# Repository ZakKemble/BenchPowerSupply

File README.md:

Bench Power Supply
==================

A 7.5A adjustable output bench power supply designed to be used with a 19V laptop power supply.

https://blog.zakkemble.net/laptop-bench-power-supply/

---

Zak Kemble

contact@zakkemble.net

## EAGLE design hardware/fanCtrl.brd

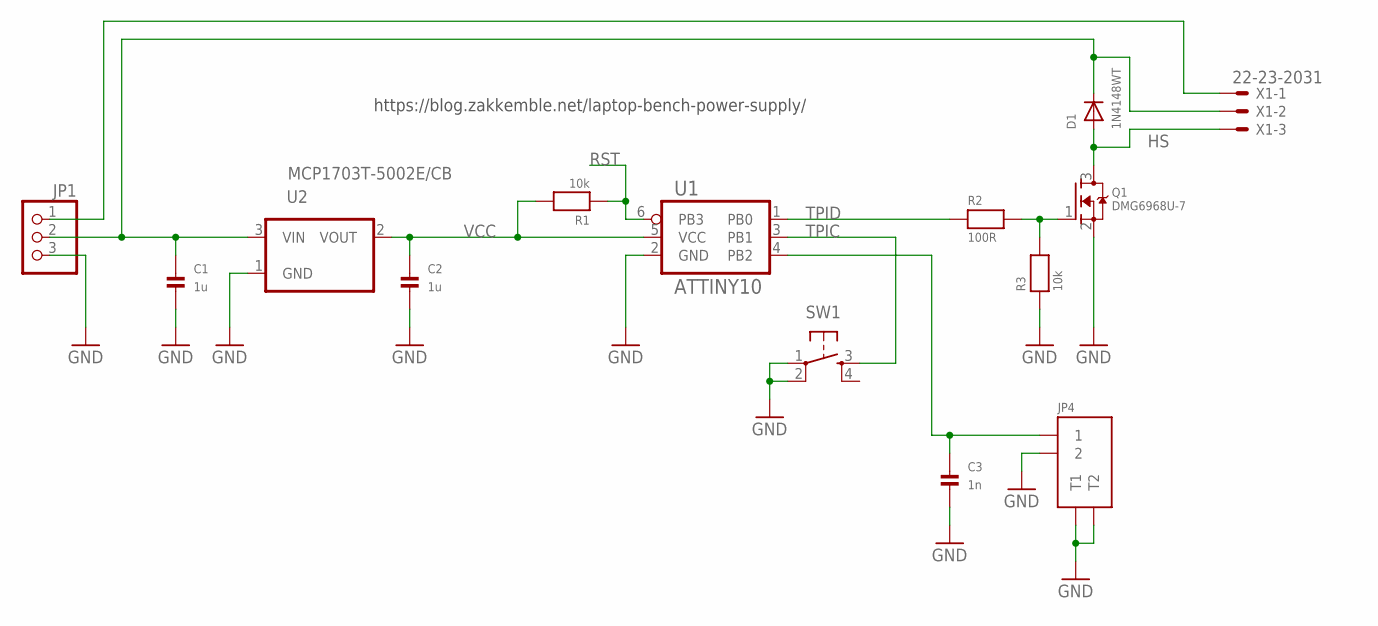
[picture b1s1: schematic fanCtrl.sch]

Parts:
C1, C2: 1u; _0603MP
C3: 1n; 0402_SMALL
D1: 1N4148WT; SOD-523
JP1: PINHD-1X3; 1X03
JP4: 2WAY
Q1: DMG6968U-7; SOT23-W
R1, R3: 10k; 0402_SMALL
R2: 100R; 0402_SMALL
SW1: SPST_TACTG75_3X4; TACT_SMD5
U1: ATTINY10; SOT23-6_SM_PAD
U2: MCP1703T-5002E/CB; SOT-23
X1: 22-23-2031

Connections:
GND: C1.2, C2.2, C3.2, JP1.3, JP4.P$2 (2), JP4.TAB$1 (T1), JP4.TAB$2 (T2), Q1.2 (S), R3.1, SW1.1, SW1.2 (P1), U1.2 (GND), U2.1 (GND)
HS: D1.A, Q1.3 (D), X1.3
unnamed: Q1.1 (G), R2.2, R3.2
unnamed: C3.1, JP4.P$1 (1), U1.4 (PB2)
unnamed: C1.1, D1.K (C), JP1.2, U2.3 (VIN), X1.2
unnamed: JP1.1, X1.1
RST: R1.1, U1.6 (PB3)
TPIC: SW1.3 (S), U1.3 (PB1)
TPID: R2.1, U1.1 (PB0)
VCC: C2.1, R1.2, U1.5 (VCC), U2.2 (VOUT)

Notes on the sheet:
https://blog.zakkemble.net/laptop-bench-power-supply/

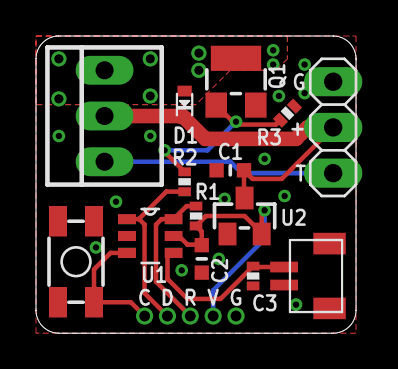
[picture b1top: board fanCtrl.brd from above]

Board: 2 copper layers, 17.8 x 16.5 mm, 14 parts (0 on the bottom side), 10 nets.

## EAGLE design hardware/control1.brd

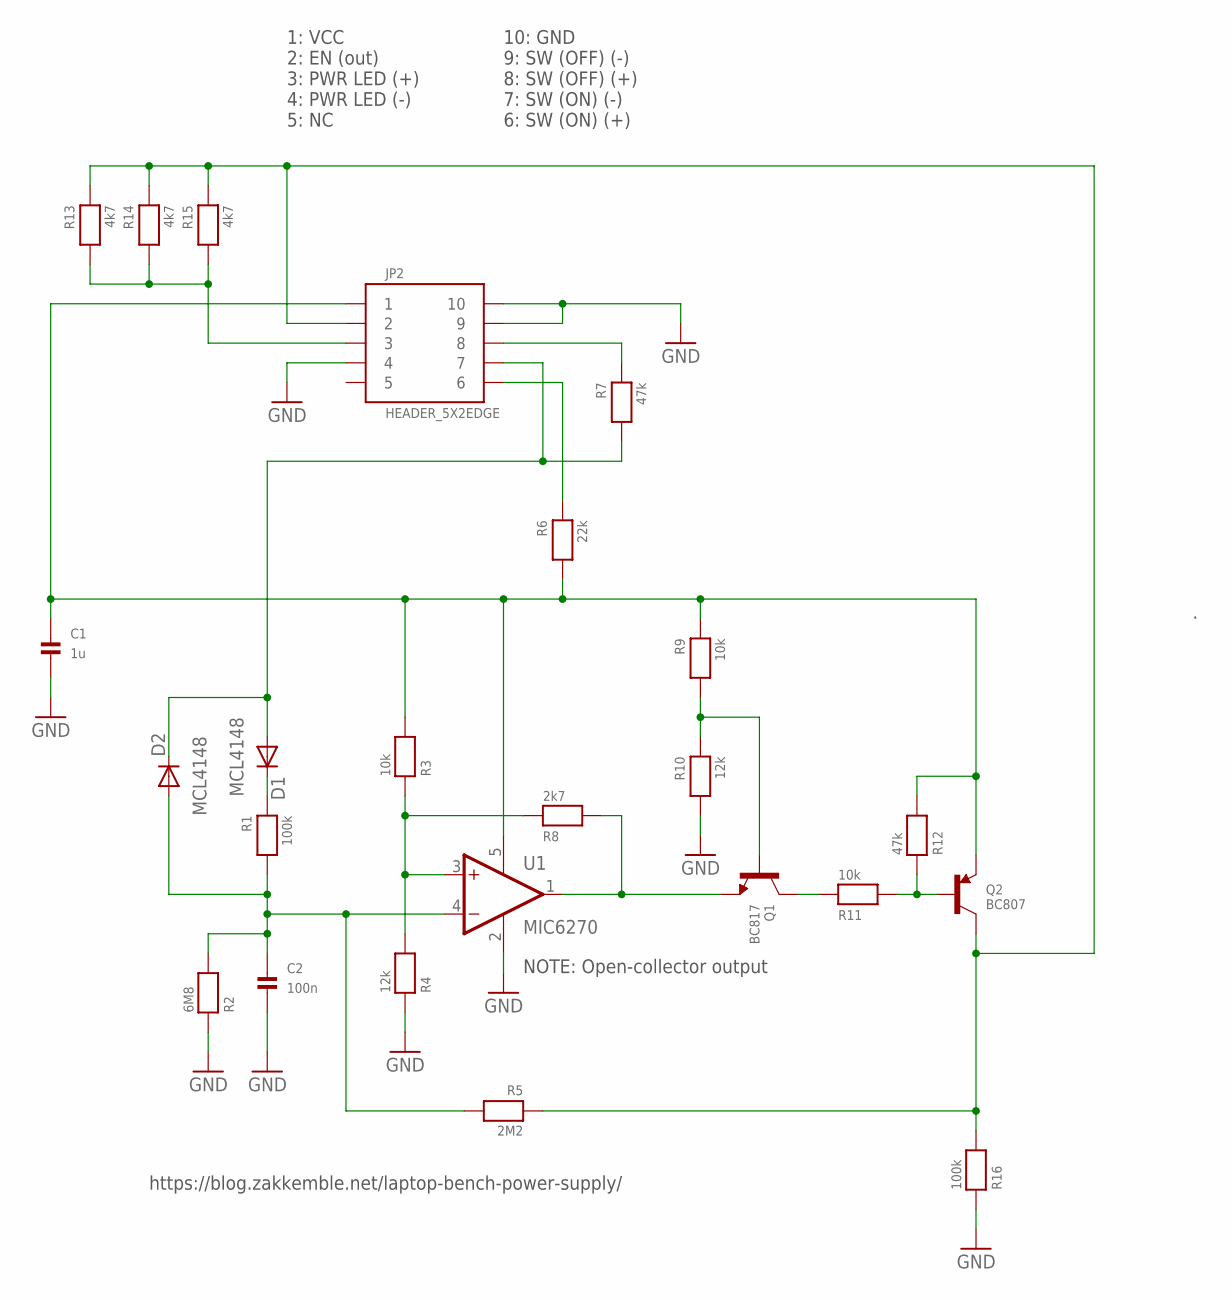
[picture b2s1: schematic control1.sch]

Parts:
C1: 1u; 0402
C2: 100n; _0603MP
D1, D2: MCL4148; MICROMELF-R
JP2: HEADER_5X2EDGE; HEADER_EDGE_5X2
Q1: BC817; SOT23-WIDE
Q2: BC807; SOT23-WIDE
R1, R16: 100k; 0402
R2: 6M8; 0402
R3, R9, R11: 10k; 0402
R4, R10: 12k; 0402
R5: 2M2; 0402
R6: 22k; 0402
R7, R12: 47k; 0402
R8: 2k7; 0402
R13, R14, R15: 4k7; 0402
U1: MIC6270; SOT95P275X110-5N

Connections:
GND: C1.2, C2.2, JP2.4, JP2.9, JP2.10, R2.1, R4.1, R10.2, R16.1, U1.2 (GND)
unnamed: C1.1, JP2.1, Q2.2 (E), R3.2, R6.2, R9.1, R12.2, U1.5 (V+)
unnamed: JP2.8, R7.1
unnamed: JP2.3, R13.2, R14.2, R15.2
unnamed: R3.1, R4.2, R8.1, U1.3 (+IN)
unnamed: C2.1, D2.A, R1.2, R2.2, R5.2, U1.4 (-IN)
unnamed: JP2.6, R6.1
unnamed: JP2.2, Q2.3 (C), R5.1, R13.1, R14.1, R15.1, R16.2
unnamed: Q1.3 (C), R11.1
unnamed: Q2.1 (B), R11.2, R12.1
unnamed: Q1.2 (E), R8.2, U1.1 (OUT)
unnamed: Q1.1 (B), R9.2, R10.1
unnamed: D1.A, D2.C, JP2.7, R7.2
unnamed: D1.C, R1.1

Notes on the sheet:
NOTE: Open-collector output
1: VCC 2: EN (out) 3: PWR LED (+) 4: PWR LED (-) 5: NC
10: GND 9: SW (OFF) (-) 8: SW (OFF) (+) 7: SW (ON) (-) 6: SW (ON) (+)
https://blog.zakkemble.net/laptop-bench-power-supply/

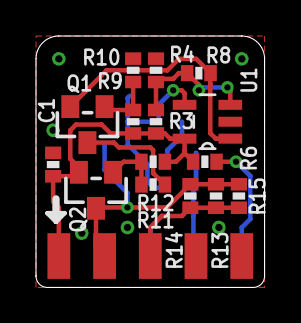
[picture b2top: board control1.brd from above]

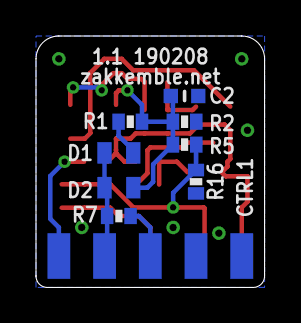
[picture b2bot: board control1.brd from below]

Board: 2 copper layers, 12.7 x 14.0 mm, 24 parts (8 on the bottom side), 14 nets.

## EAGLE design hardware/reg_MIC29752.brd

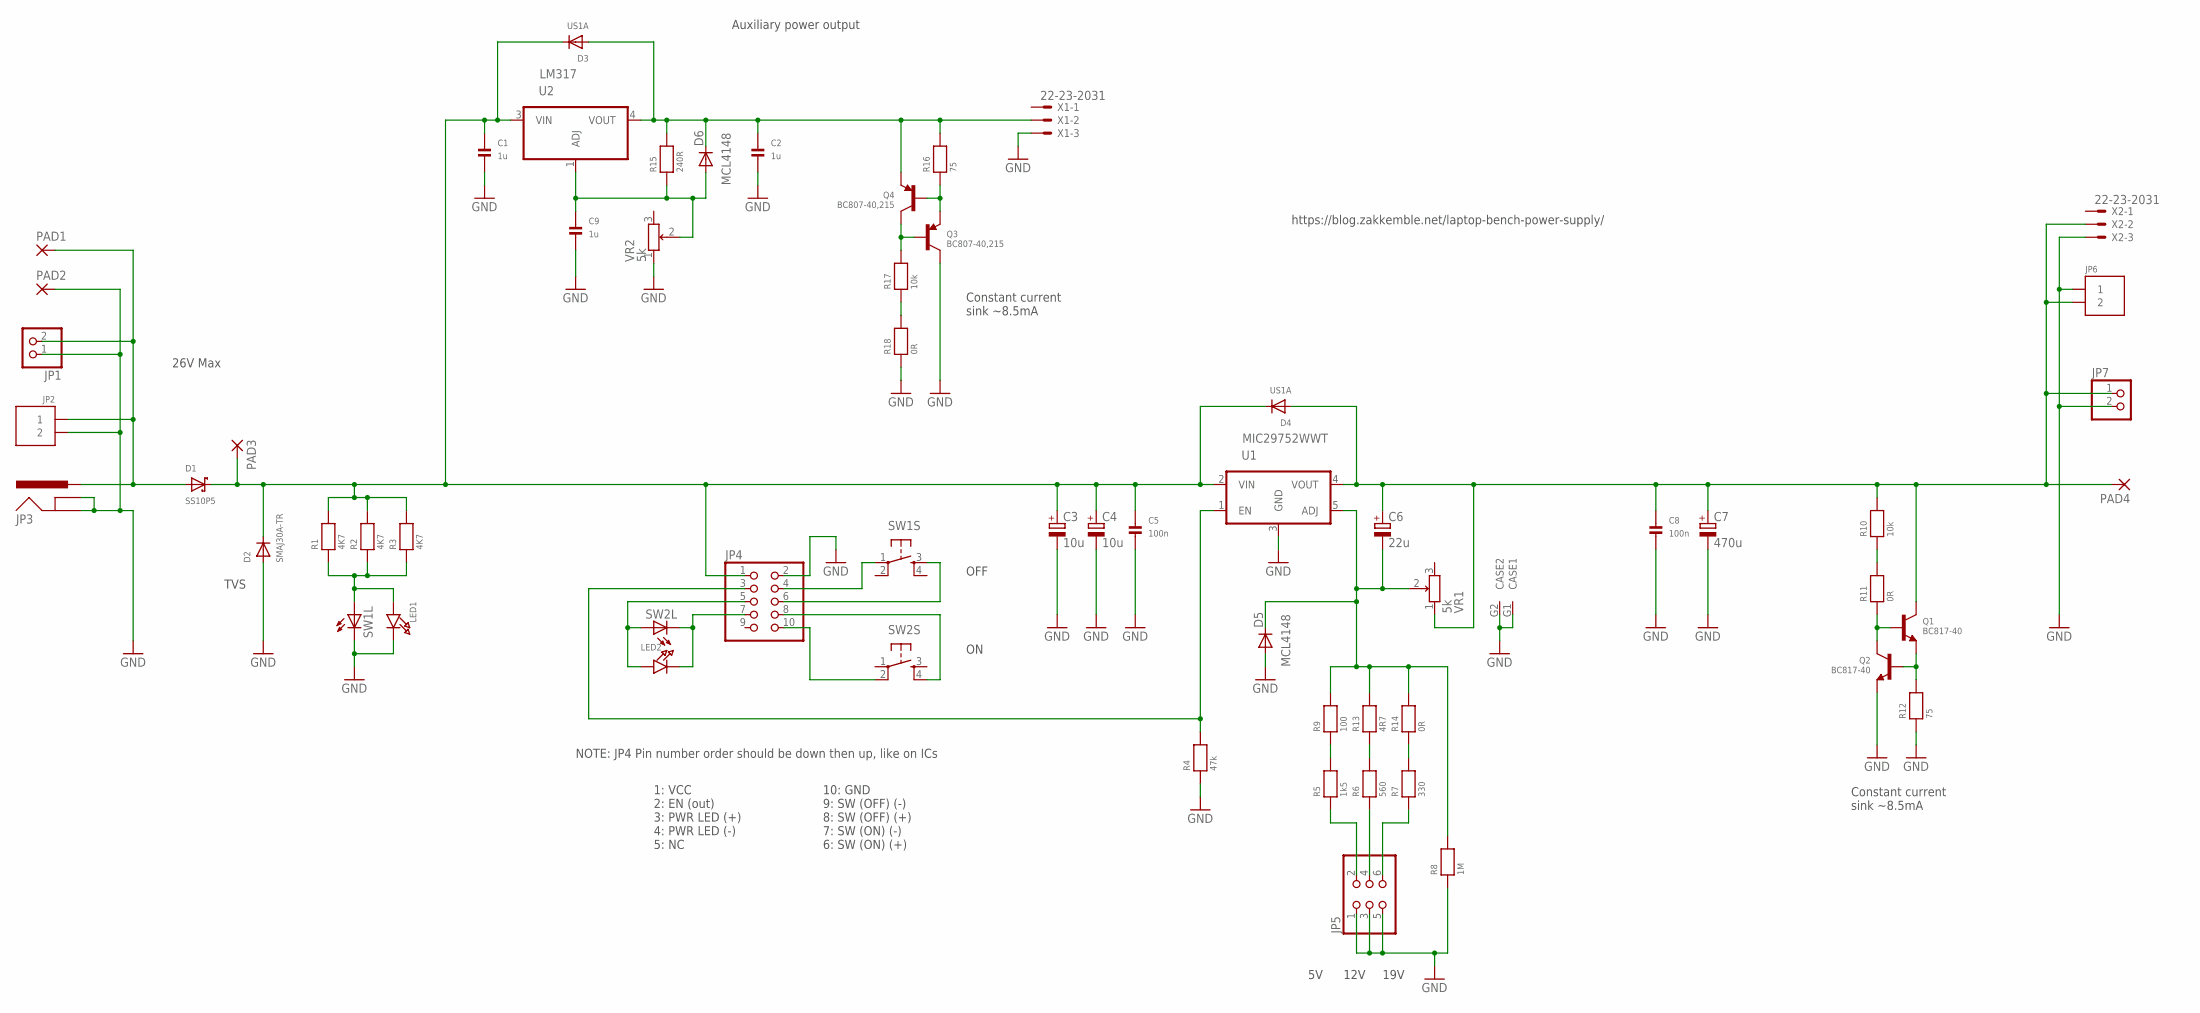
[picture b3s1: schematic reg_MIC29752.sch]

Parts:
C1, C2, C9: 1u; 0805_NO_OUTLINE
C3, C4: 10u; E2-5
C5, C8: 100n; _0603MP
C6: 22u; E2-4
C7: 470u; E5-10,5
D1: SS10P5; TO-277A
D2: SMAJ30A-TR; SMADIODE
D3, D4: US1A; SMADIODE
D5, D6: MCL4148; MICROMELF-R
JP1, JP7: PINHD-1X2; 1X02
JP2, JP6: TERM_BLOCK_2WAY; TERM_2WAY
JP3: POWER_JACKPTH_HIGHCURRENT; POWER_JACK_PTH_HIGHCURRENT
JP4: PINHD-2X5; 2X05
JP5: PINHD-2X3; 2X03
LED1, LED2: LED0603_NOOUTLINE; CHIPLED_0603_NOOUTLINE
PAD1, PAD2, PAD3, PAD4: WIREPAD-3.81,2SCREW-3MM; SCREWPAD-3MM
Q1: BC817-40; SOT23-W
Q2: BC817-40; SOT23-WIDE
Q3: BC807-40,215; SOT23-W
Q4: BC807-40,215; SOT23-WIDE
R1, R2, R3: 4K7; 0402
R4: 47k; 0402
R5: 1k5; 0402
R6: 560; 0402
R7: 330; 0402
R8: 1M; 0402
R9: 100; 0402
R10, R17: 10k; 0402
R11, R14, R18: 0R; 0402
R12, R16: 75; 0402
R13: 4R7; 0402
R15: 240R; 0402
SW1, SW2: SPST_TACT_LED12MM_TH; TACT_TH_12MM_LED
U1: MIC29752WWT; TO247-5-REVERSE
U2: LM317; DPAK
VR1: 5k; RV09
VR2: 5k; TRIMPOT_BOURNS3MM
X1, X2: 22-23-2031

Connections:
GND: C1.2, C2.2, C3.-, C4.-, C5.2, C7.-, C8.2, C9.2, D2.A, D5.A, JP1.1, JP2.2, JP3.C1 (GNDBREAK), JP3.C2 (GNDBREAK), JP3.C3 (GNDBREAK), JP3.C4 (GNDBREAK), JP3.GND, JP4.2, JP5.1, JP5.3, JP5.5, JP6.1, JP7.2, LED1.C, PAD2.1, Q2.2 (E), Q3.3 (C), R4.1, R8.1, R12.1, R18.1, SW1.5 (C), U1.3 (GND), VR1.G1 (CASE1), VR1.G2 (CASE2), VR2.1 (1A), X1.3, X2.3
unnamed: C1.1, C3.+, C4.+, C5.1, D1.K (C), D2.C, D3.C, D4.C, JP4.1, PAD3.1, R1.2, R2.2, R3.2, U1.2 (VIN), U2.3 (VIN)
unnamed: LED1.A, R1.1, R2.1, R3.1, SW1.6 (A)
unnamed: D1.1 (A), D1.2 (A), JP1.2, JP2.1, JP3.PWR, PAD1.1
unnamed: R5.2, R9.1
unnamed: JP4.7, LED2.C, SW2.5 (C)
unnamed: R10.1, R11.2
unnamed: R6.2, R13.1
unnamed: JP4.10, SW2.2 (P1)
unnamed: JP4.8, SW2.4 (S1)
unnamed: C2.1, D3.A, D6.C, Q4.2 (E), R15.2, R16.2, U2.4 (VOUT), X1.2
unnamed: R7.2, R14.1
unnamed: JP4.6, SW1.3 (S)
unnamed: JP4.4, SW1.1
unnamed: C6.-, D5.C, R8.2, R9.2, R13.2, R14.2, U1.5 (ADJ), VR1.2 (1S)
unnamed: JP5.6, R7.1
unnamed: JP5.4, R6.1
unnamed: C9.1, D6.A, R15.1, U2.1 (ADJ), VR2.2 (1S)
unnamed: C6.+, C7.+, C8.1, D4.A, JP6.2, JP7.1, PAD4.1, Q1.3 (C), R10.2, U1.4 (VOUT), VR1.1 (1A), X2.2
unnamed: JP5.2, R5.1
unnamed: Q1.2 (E), Q2.1 (B), R12.2
unnamed: Q1.1 (B), Q2.3 (C), R11.1
unnamed: Q3.2 (E), Q4.1 (B), R16.1
unnamed: Q3.1 (B), Q4.3 (C), R17.2
unnamed: R17.1, R18.2
unnamed: JP4.3, R4.2, U1.1 (EN)
unnamed: JP4.5, LED2.A, SW2.6 (A)

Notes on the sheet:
1: VCC 2: EN (out) 3: PWR LED (+) 4: PWR LED (-) 5: NC
10: GND 9: SW (OFF) (-) 8: SW (OFF) (+) 7: SW (ON) (-) 6: SW (ON) (+)
NOTE: JP4 Pin number order should be down then up, like on ICs
OFF
Constant current sink ~8.5mA
Auxiliary power output
https://blog.zakkemble.net/laptop-bench-power-supply/
12V
19V
26V Max
TVS

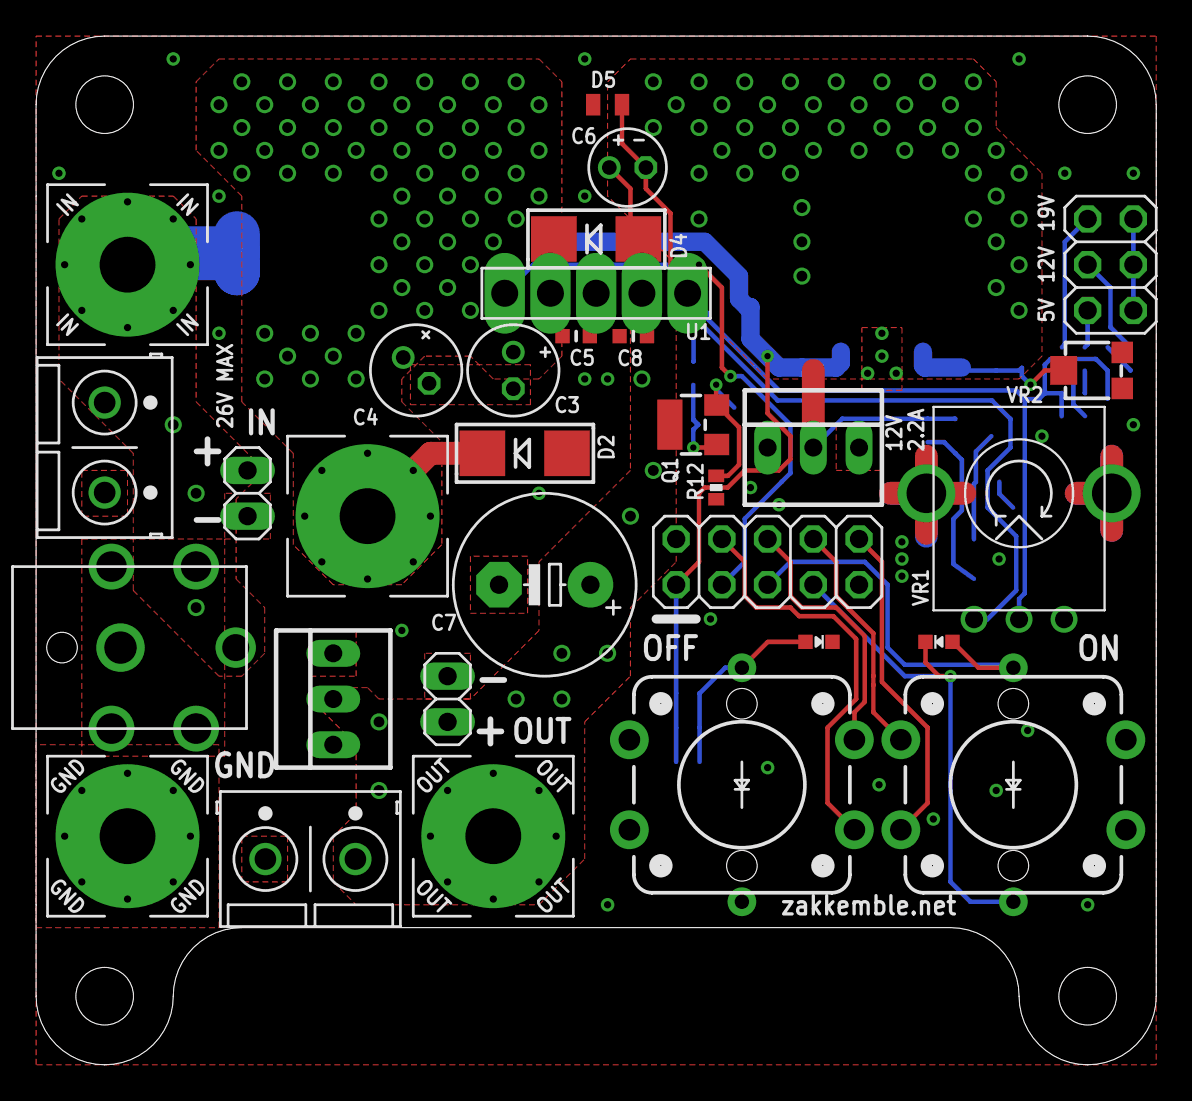
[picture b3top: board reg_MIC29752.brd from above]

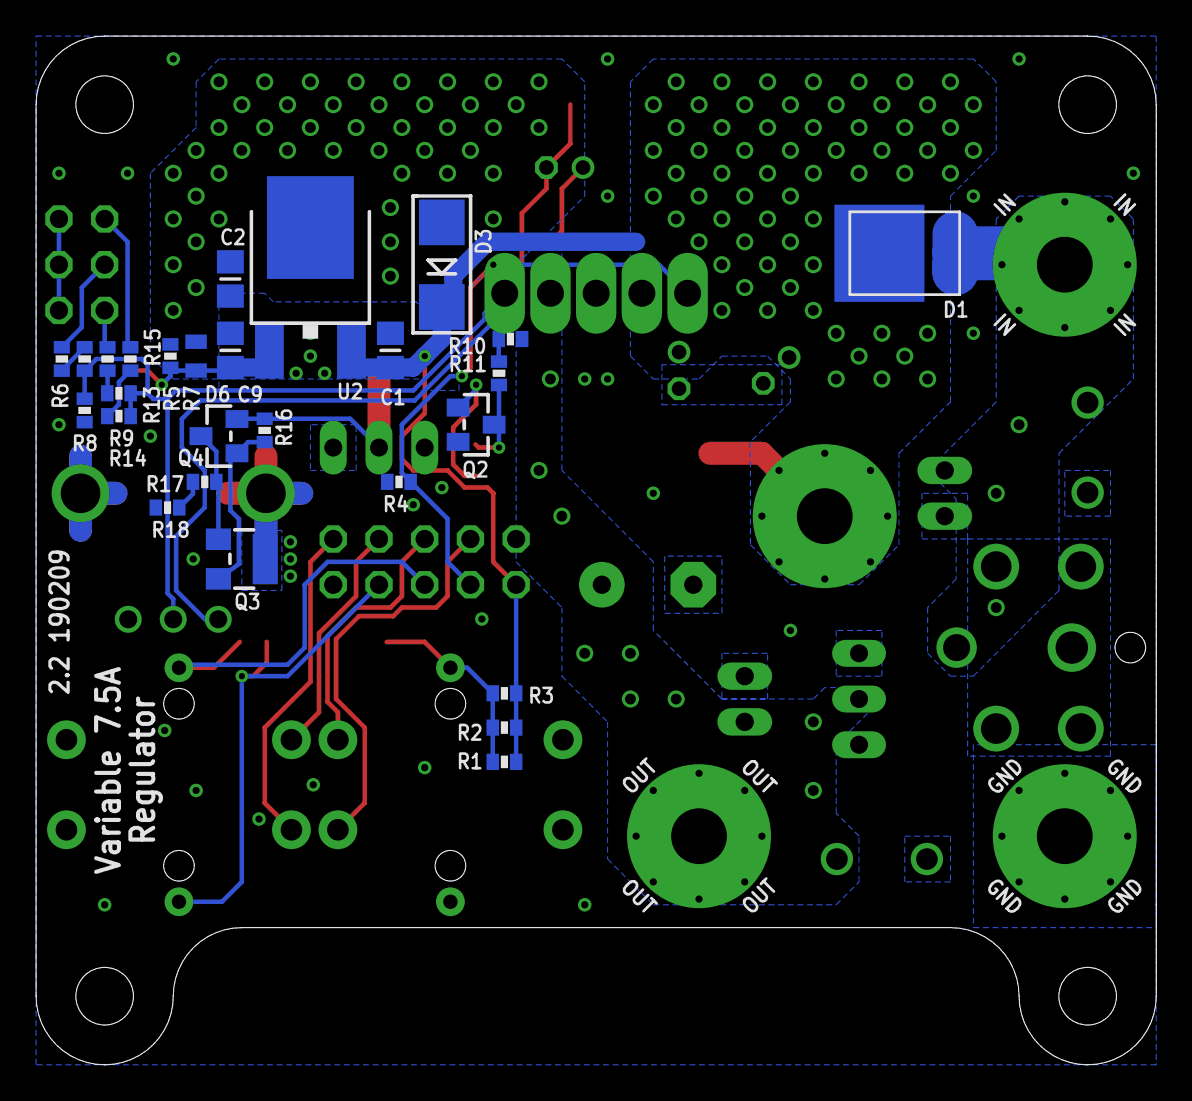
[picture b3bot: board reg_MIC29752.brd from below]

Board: 2 copper layers, 62.2 x 57.1 mm, 58 parts (27 on the bottom side), 27 nets.

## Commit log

2019-09-30 Added files

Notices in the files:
parts and their libraries:
microbuilder: This work is placed in the public domain, and may be freely used for commercial and non-commercial work with the following conditions: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
